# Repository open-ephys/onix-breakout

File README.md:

# ONIX Breakout Board
This board allows bench access to the IO provided by the [ONIX FMC Host
Board](https://github.com/open-ephys/onix-fmc-host). It features:

- 4x coax headstage ports, each with a physical power switch
- BNC, IDC (ribbon), or direct wire access to 12 analog inputs or outputs
- IDC (ribbon) or direct wire access to 8 digital outputs and 8 digital inputs
  (5 volt tolerate)
- 6x buttons for marking experimental events
- 41x state-indication LEDs
- 3x high-speed clock feed throughs
- Full-speed, USB 2.0 access to the onboard [TinyFPGA
  BX](https://www.crowdsupply.com/tinyfpga/tinyfpga-bx) for communication,
  programming, and customization 
- [HARP bus](https://www.cf-hw.org/harp)
- Rugged M6 or 1/4-20 mounting options compliant with 19" racks and optical
  tables
- Open-source [gateware](./gateware) created using open-source FPGA toolchain:
  [yosys](http://www.clifford.at/yosys/) & [nextpnr](https://github.com/YosysHQ/nextpnr)

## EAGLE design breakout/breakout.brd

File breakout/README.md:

## Bill of Materials
The bill of materials for this device can be found
[here](https://docs.google.com/spreadsheets/d/1dZ0ANEF8czLGsupTHfIfsVSbmfPmiTM9wAFmvc-KBbU/edit?usp=sharing).

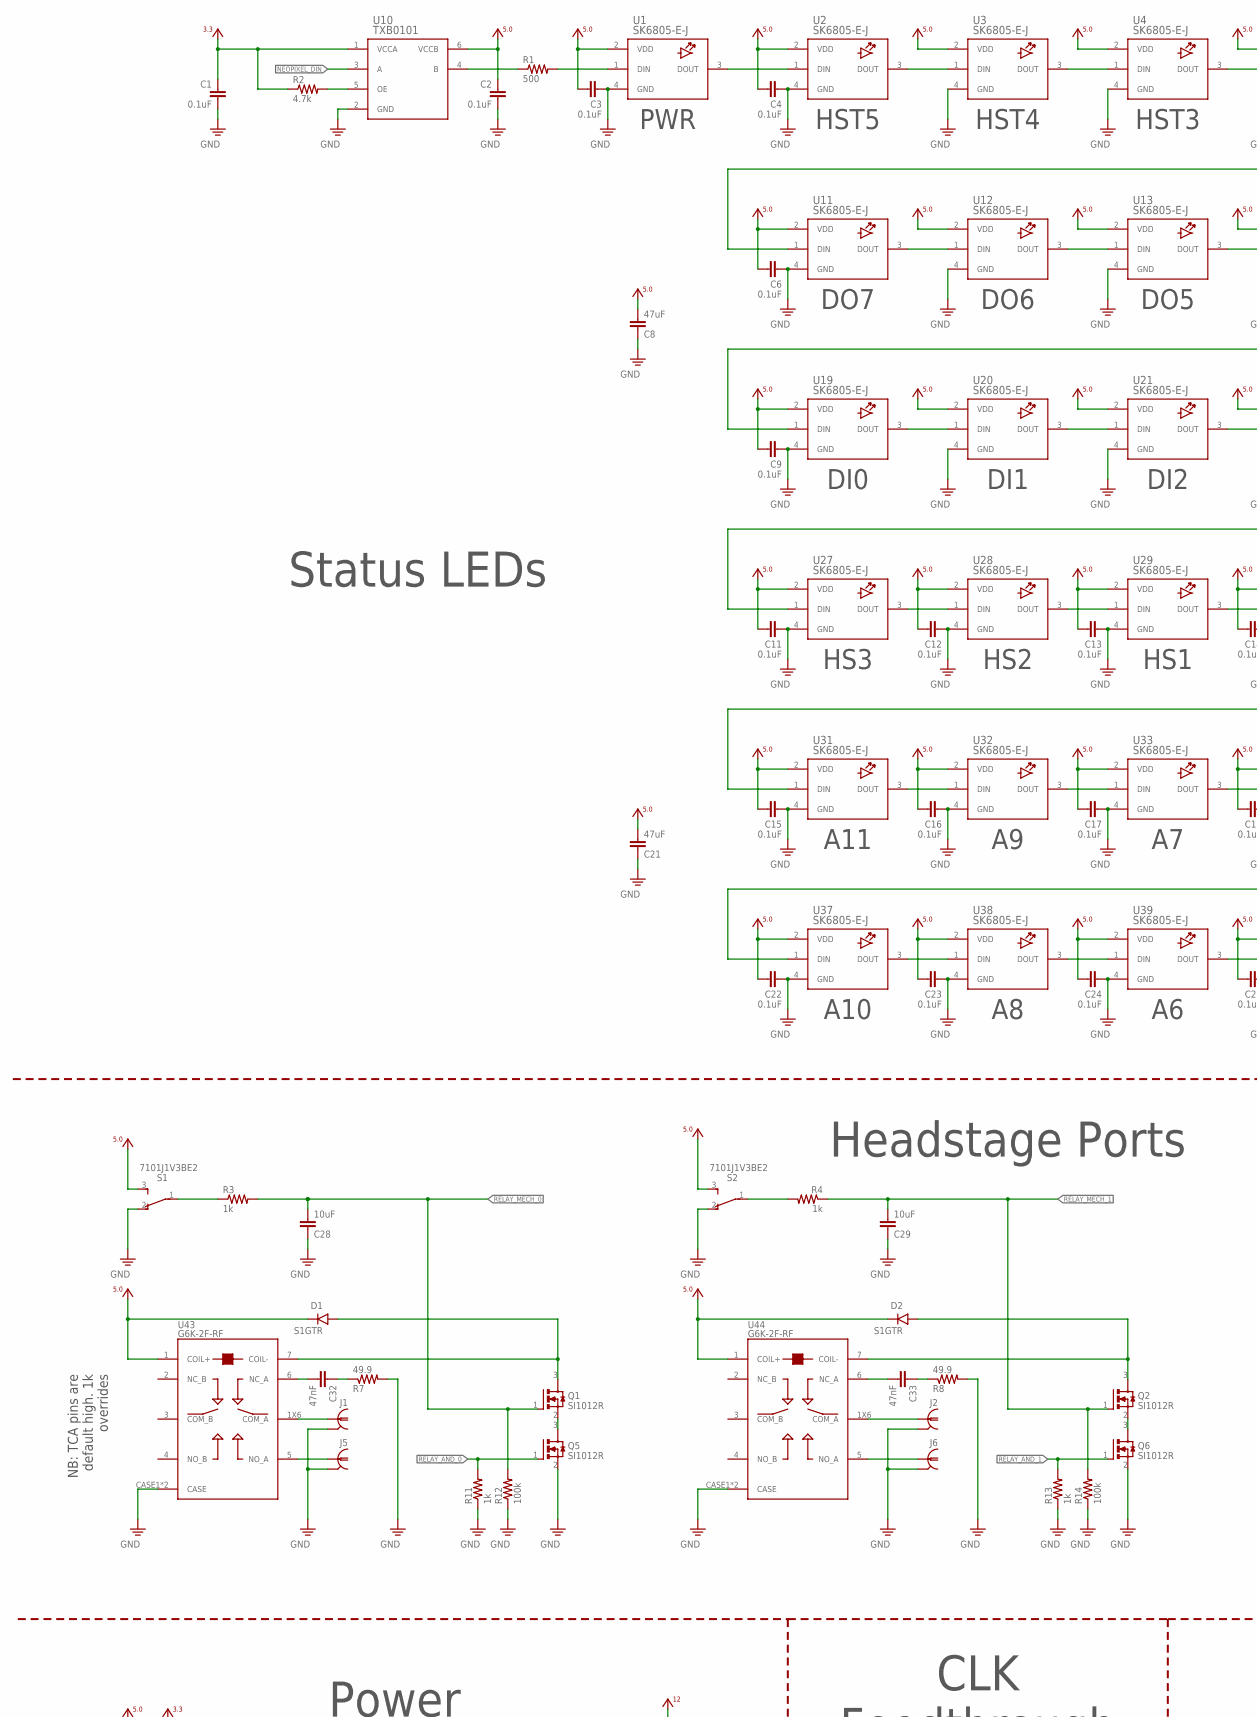
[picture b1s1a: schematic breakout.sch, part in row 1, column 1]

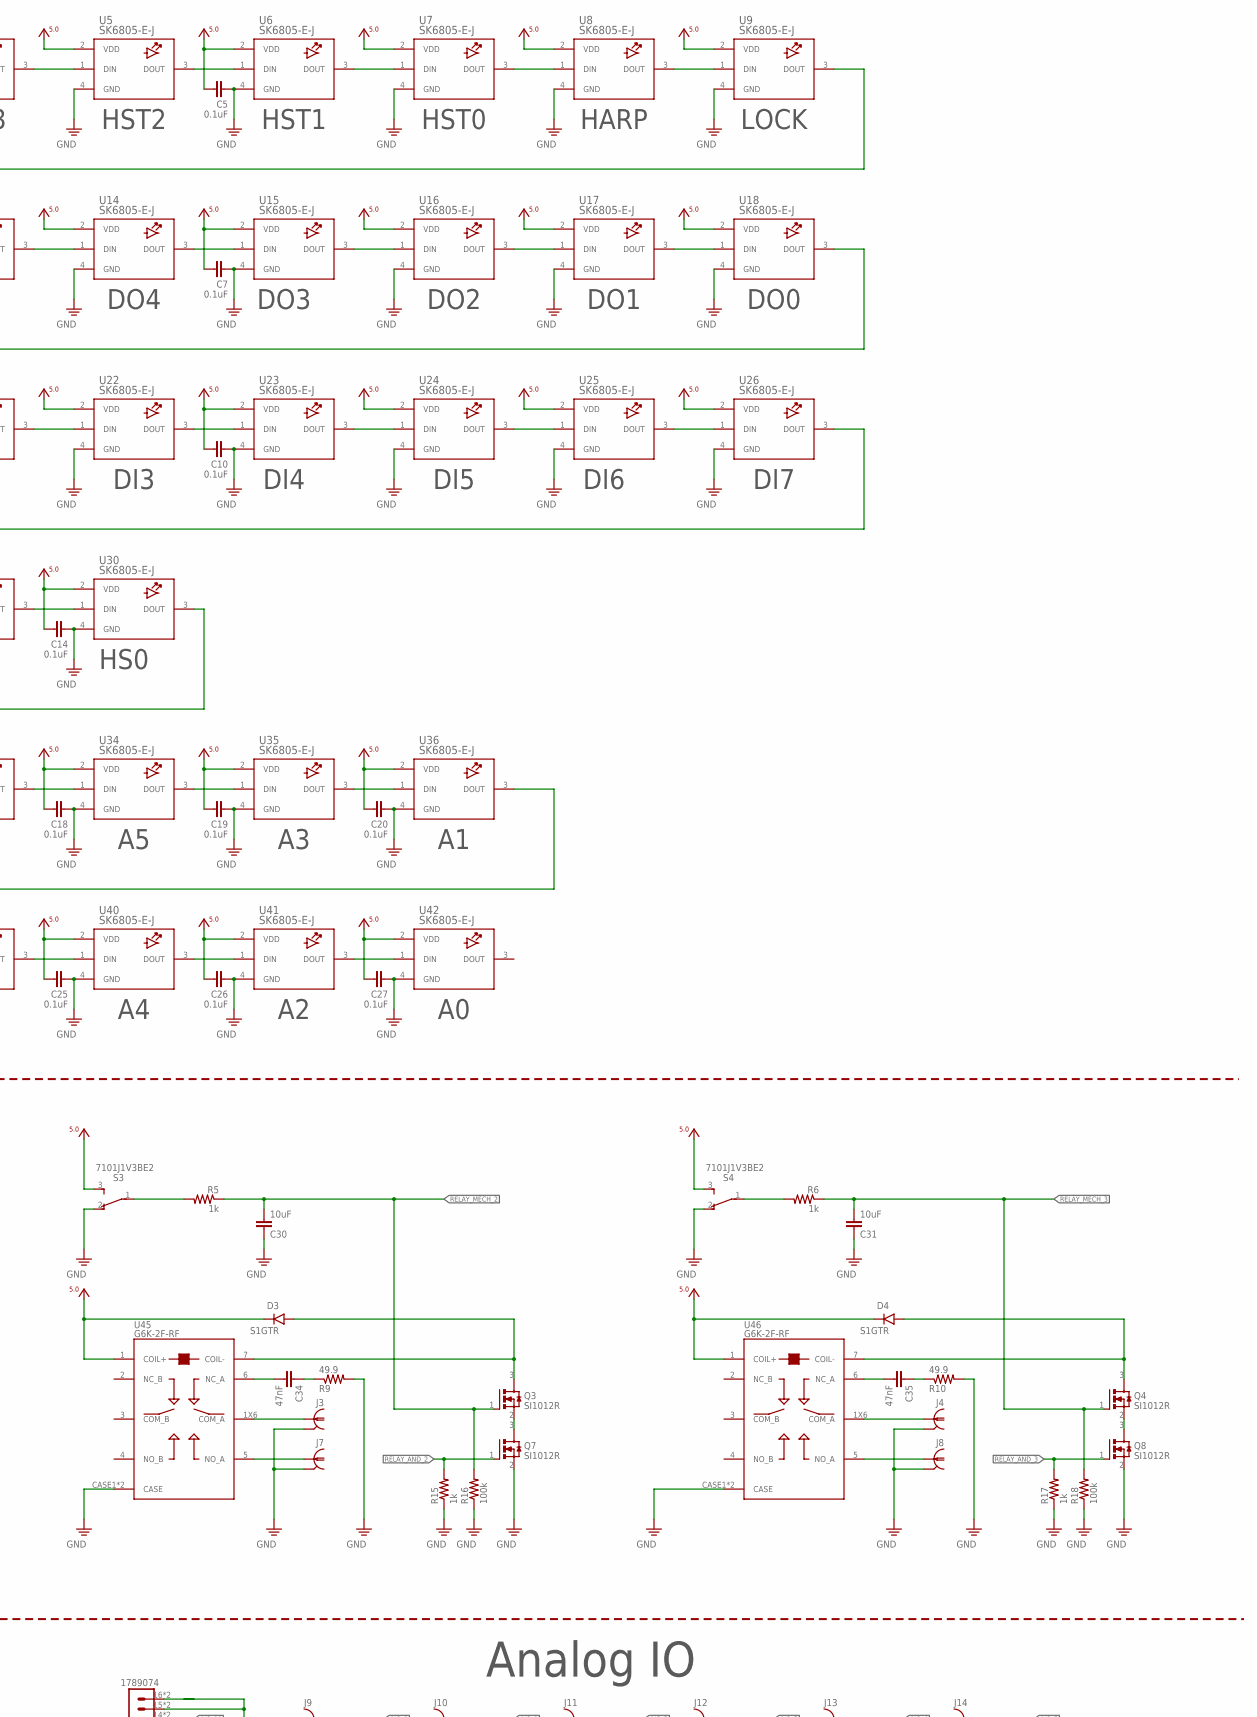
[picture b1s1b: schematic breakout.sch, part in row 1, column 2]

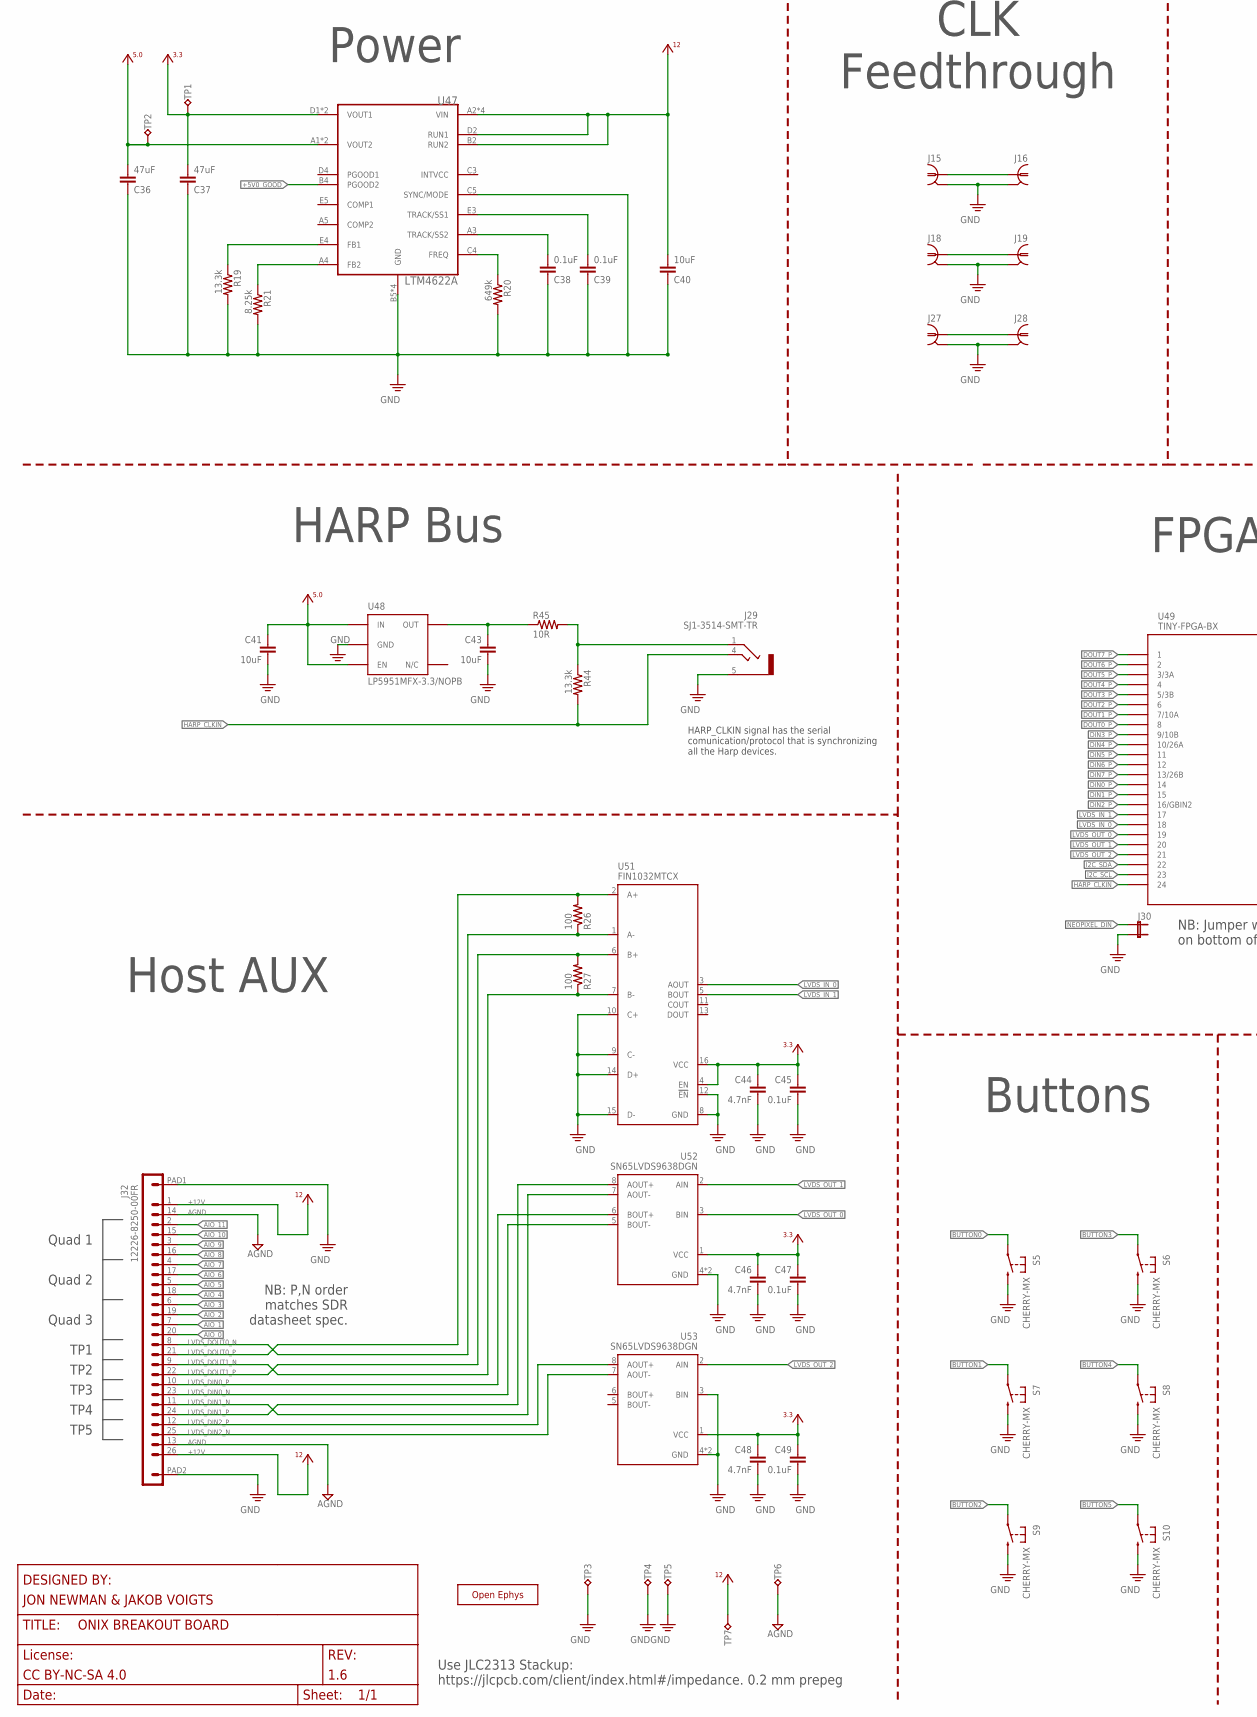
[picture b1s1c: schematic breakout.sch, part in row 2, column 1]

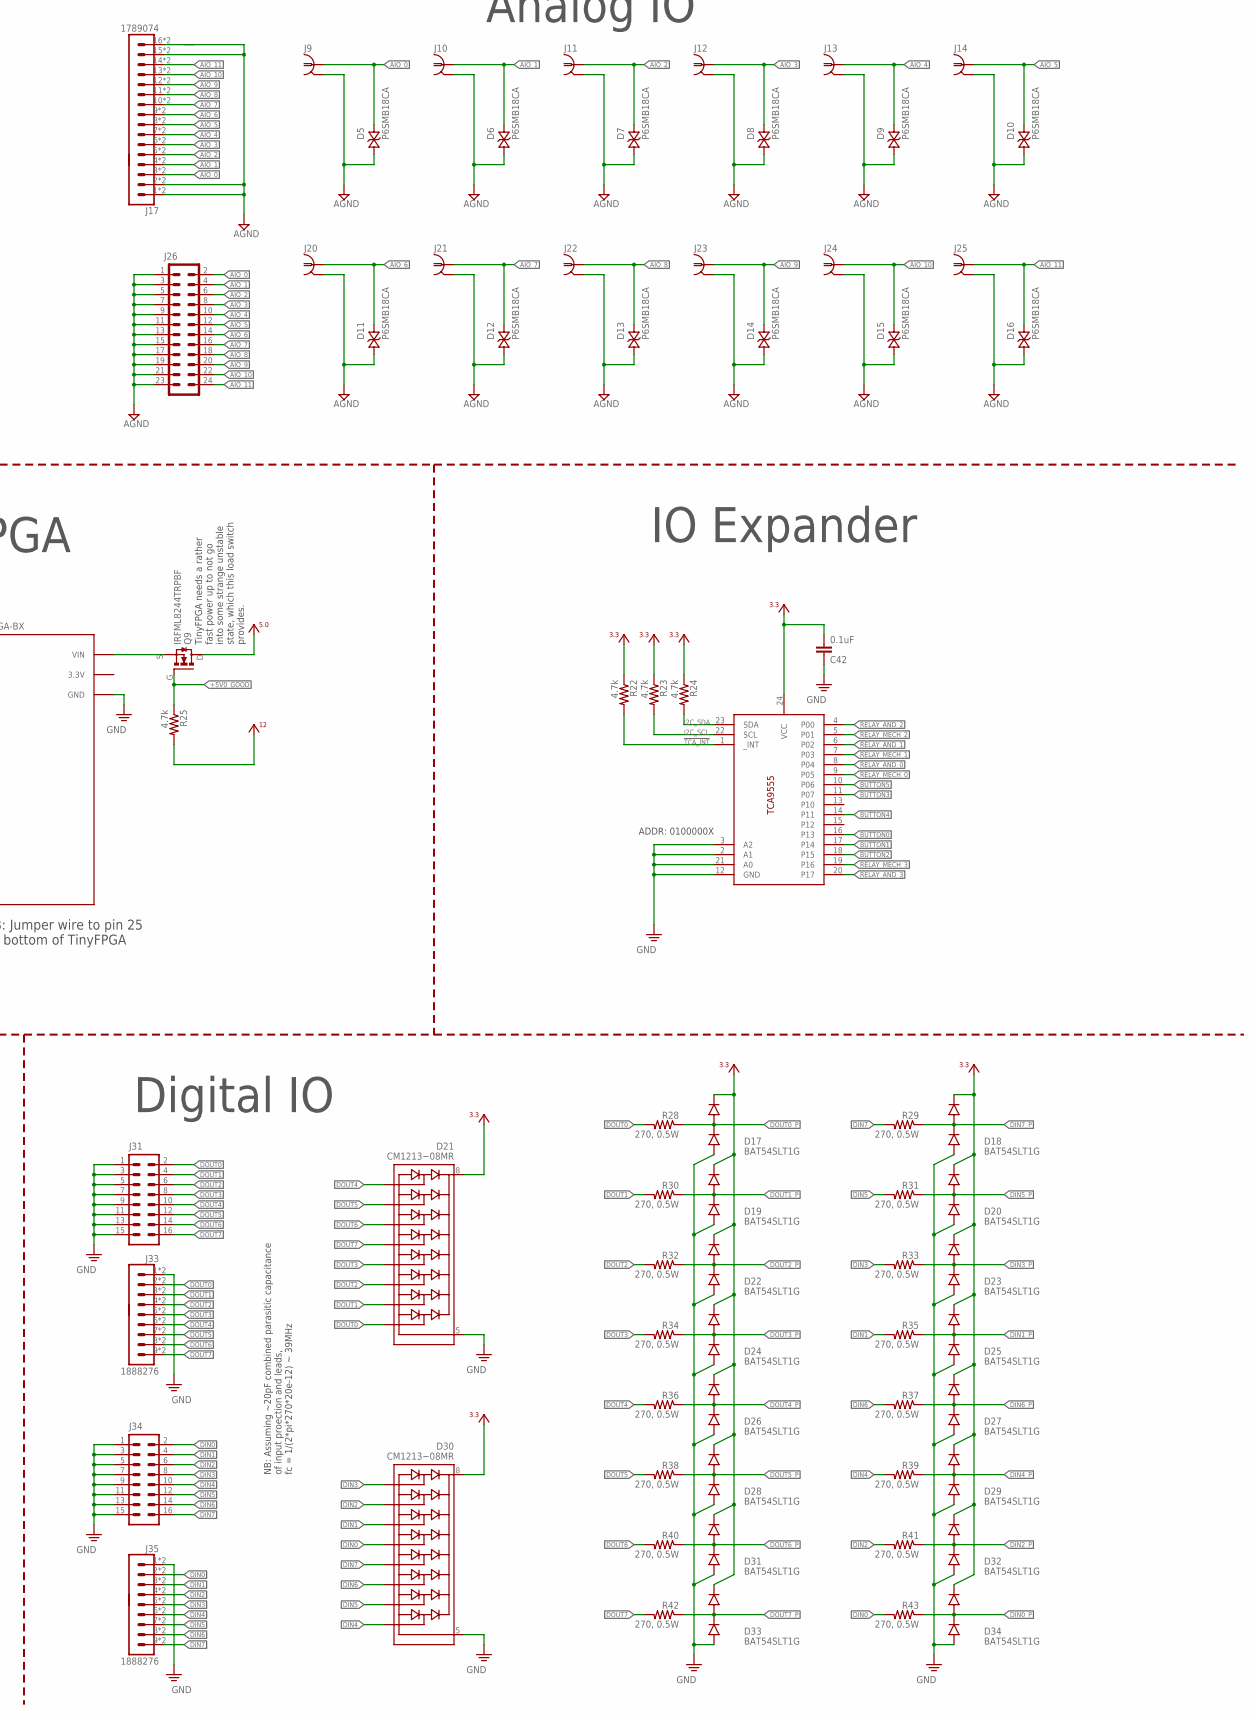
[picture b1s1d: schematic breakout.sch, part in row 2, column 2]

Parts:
C1, C2, C3, C4, C5, C6, C7, C9, C10, C11, C12, C13, C14, C15, C16, C17, C18, C19, C20, C22, C23, C24, C25, C26, C27, C38, C39, C42, C45, C47, C49: 0.1uF; 0402
C8, C21, C36, C37: 47uF; 1210
C28, C29, C30, C31, C40, C41, C43: 10uF; 0805
C32, C33, C34, C35: 47nF; 0402
C44, C46, C48: 4.7nF; 0402
D1, D2, D3, D4: S1GTR; SMA-DO214AC
D5, D6, D7, D8, D9, D10, D11, D12, D13, D14, D15, D16: P6SMB18CA; SMA-DO214AC
D17, D18, D19, D20, D22, D23, D24, D25, D26, D27, D28, D29, D31, D32, D33, D34: BAT54SLT1G; SOT23
D21, D30: CM1213−08MR; MSOP-10-3X3
J1, J2, J3, J4, J16, J19, J28: COAX_SMA-VERT; SMA_JACK_142-0701-201
J5, J6, J7, J8, J15, J18, J27: COAX_MMCX-THRU; MMCX-THRU
J9, J10, J11, J12, J13, J14, J20, J21, J22, J23, J24, J25: COAX_0731010360; 0731010360
J17: 1789074; SCREW16-2
J26: 69168-124HLF; 2X12-BIG
J29: SJ1-3514-SMT-TR; 35RASMT2BHNTRX
J30: JP2E_THRU-HOLE; JP2
J31, J34: 69168-116HLF; 2X08-BIG
J32: 12226-8250-00FR; 12226-82X0-00XX
J33, J35: 1888276; SCREW9-2
Q1, Q2, Q3, Q4, Q5, Q6, Q7, Q8: SI1012R; SC75
Q9: IRFML8244TRPBF; SOT23-GSD
R1: 500; 0402
R2, R22, R23, R24, R25: 4.7k; 0402
R3, R4, R5, R6, R11, R13, R15, R17: 1k; 0402
R7, R8, R9, R10: 49.9; 0402
R12, R14, R16, R18: 100k; 0402
R19, R44: 13.3k; 0402
R20: 649k; 0402
R21: 8.25k; 0402
R26, R27: 100; 0402
R28, R29, R30, R31, R32, R33, R34, R35, R36, R37, R38, R39, R40, R41, R42, R43: 270, 0.5W; 0805
R45: 10R; 0402
S1, S2, S3, S4: 7101J1V3BE2; CK_7101J1V3QE2
S5, S6, S7, S8, S9, S10: CHERRY-MX
TP1, TP2: TPTP19R; TP19R
TP3, TP4, TP5, TP6, TP7: TP_2MM; TESTPOINT_2MM
U1, U2, U3, U4, U5, U6, U7, U8, U9, U11, U12, U13, U14, U15, U16, U17, U18, U19, U20, U21, U22, U23, U24, U25, U26, U27, U28, U29, U30, U31, U32, U33, U34, U35, U36, U37, U38, U39, U40, U41, U42: SK6805-E-J; NEOPIXEL-1.5X1.5
U10: TXB0101; SOT23-6
U43, U44, U45, U46: G6K-2F-RF; G6KU-2F-RF
U47: LTM4622A; BGA_5X5_625X625
U48: LP5951MFX-3.3/NOPB; TSOT23-5; MPN TLV70033DDCR
U49: TINY-FPGA-BX; TINY-FPGA-BX_BASIC
U50: TCA9555; TSSOP-24
U51: FIN1032MTCX; TSSOP-16
U52, U53: SN65LVDS9638DGN; MSOP-8-PAD-3X3
X: OE-LOGO_28X20; OE-LOGO-28X20

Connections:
!TCA_INT: R22.2, U50.1 (_INT)
+3V3: C1.1, C37.2, C42.2, C44.1, C45.1, C46.1, C47.1, C48.1, C49.1, D17.2 (C), D18.2 (C), D19.2 (C), D20.2 (C), D21.8 (VCC), D22.2 (C), D23.2 (C), D24.2 (C), D25.2 (C), D26.2 (C), D27.2 (C), D28.2 (C), D29.2 (C), D30.8 (VCC), D31.2 (C), D32.2 (C), D33.2 (C), D34.2 (C), R2.1, R22.1, R23.1, R24.1, TP1.TP, U10.1 (VCCA), U47.D1 (VOUT1), U47.E1 (VOUT1), U50.24 (VCC), U51.4 (EN), U51.16 (VCC), U52.1 (VCC), U53.1 (VCC)
+5V0: C2.1, C3.2, C4.2, C5.2, C6.2, C7.2, C8.2, C9.2, C10.2, C11.2, C12.2, C13.2, C14.2, C15.2, C16.2, C17.2, C18.2, C19.2, C20.2, C21.2, C22.2, C23.2, C24.2, C25.2, C26.2, C27.2, C36.2, C41.1, D1.C, D2.C, D3.C, D4.C, Q9.D, S1.3, S2.3, S3.3, S4.3, TP2.TP, U1.2 (VDD), U2.2 (VDD), U3.2 (VDD), U4.2 (VDD), U5.2 (VDD), U6.2 (VDD), U7.2 (VDD), U8.2 (VDD), U9.2 (VDD), U10.6 (VCCB), U11.2 (VDD), U12.2 (VDD), U13.2 (VDD), U14.2 (VDD), U15.2 (VDD), U16.2 (VDD), U17.2 (VDD), U18.2 (VDD), U19.2 (VDD), U20.2 (VDD), U21.2 (VDD), U22.2 (VDD), U23.2 (VDD), U24.2 (VDD), U25.2 (VDD), U26.2 (VDD), U27.2 (VDD), U28.2 (VDD), U29.2 (VDD), U30.2 (VDD), U31.2 (VDD), U32.2 (VDD), U33.2 (VDD), U34.2 (VDD), U35.2 (VDD), U36.2 (VDD), U37.2 (VDD), U38.2 (VDD), U39.2 (VDD), U40.2 (VDD), U41.2 (VDD), U42.2 (VDD), U43.1 (COIL+), U44.1 (COIL+), U45.1 (COIL+), U46.1 (COIL+), U47.A1 (VOUT2), U47.B1 (VOUT2), U48.1 (IN), U48.3 (EN)
+5V0_GOOD: Q9.G, R25.1, U47.B4 (PGOOD2)
+12V: C40.2, J32.1, J32.26, R25.2, TP7.1, U47.A2 (VIN), U47.B2 (RUN2), U47.B3 (VIN), U47.D2 (RUN1), U47.D3 (VIN), U47.E2 (VIN)
AGND: D5.A (1), D6.A (1), D7.A (1), D8.A (1), D9.A (1), D10.A (1), D11.A (1), D12.A (1), D13.A (1), D14.A (1), D15.A (1), D16.A (1), J9.2, J9.3 (2), J9.4 (2), J9.5 (2), J10.2, J10.3 (2), J10.4 (2), J10.5 (2), J11.2, J11.3 (2), J11.4 (2), J11.5 (2), J12.2, J12.3 (2), J12.4 (2), J12.5 (2), J13.2, J13.3 (2), J13.4 (2), J13.5 (2), J14.2, J14.3 (2), J14.4 (2), J14.5 (2), J17.1, J17.2, J17.15, J17.16, J17.17 (1), J17.18 (2), J17.31 (15), J17.32 (16), J20.2, J20.3 (2), J20.4 (2), J20.5 (2), J21.2, J21.3 (2), J21.4 (2), J21.5 (2), J22.2, J22.3 (2), J22.4 (2), J22.5 (2), J23.2, J23.3 (2), J23.4 (2), J23.5 (2), J24.2, J24.3 (2), J24.4 (2), J24.5 (2), J25.2, J25.3 (2), J25.4 (2), J25.5 (2), J26.1, J26.3, J26.5, J26.7, J26.9, J26.11, J26.13, J26.15, J26.17, J26.19, J26.21, J26.23, J32.13, J32.14, TP6.1
AIO_0: D5.C (2), J9.1, J17.3, J17.19 (3), J26.2, J32.20
AIO_1: D6.C (2), J10.1, J17.4, J17.20 (4), J26.4, J32.7
AIO_2: D7.C (2), J11.1, J17.5, J17.21 (5), J26.6, J32.19
AIO_3: D8.C (2), J12.1, J17.6, J17.22 (6), J26.8, J32.6
AIO_4: D9.C (2), J13.1, J17.7, J17.23 (7), J26.10, J32.18
AIO_5: D10.C (2), J14.1, J17.8, J17.24 (8), J26.12, J32.5
AIO_6: D11.C (2), J17.9, J17.25 (9), J20.1, J26.14, J32.17
AIO_7: D12.C (2), J17.10, J17.26 (10), J21.1, J26.16, J32.4
AIO_8: D13.C (2), J17.11, J17.27 (11), J22.1, J26.18, J32.16
AIO_9: D14.C (2), J17.12, J17.28 (12), J23.1, J26.20, J32.3
AIO_10: D15.C (2), J17.13, J17.29 (13), J24.1, J26.22, J32.15
AIO_11: D16.C (2), J17.14, J17.30 (14), J25.1, J26.24, J32.2
BUTTON0: S5.SW1, U50.16 (P13)
BUTTON1: S7.SW1, U50.17 (P14)
BUTTON2: S9.SW1, U50.18 (P15)
BUTTON3: S6.SW1, U50.11 (P07)
BUTTON4: S8.SW1, U50.14 (P11)
BUTTON5: S10.SW1, U50.10 (P06)
DIN0: D30.4 (CH4), J34.2, J35.2, J35.11 (2), R43.2
DIN0_P: D34.3 (COMM), R43.1, U49.14
DIN1: D30.3 (CH3), J34.4, J35.3, J35.12 (3), R35.2
DIN1_P: D25.3 (COMM), R35.1, U49.15
DIN2: D30.2 (CH2), J34.6, J35.4, J35.13 (4), R41.2
DIN2_P: D32.3 (COMM), R41.1, U49.16 (16/GBIN2)
DIN3: D30.1 (CH1), J34.8, J35.5, J35.14 (5), R33.2
DIN3_P: D23.3 (COMM), R33.1, U49.9 (9/10B)
DIN4: D30.10 (CH8), J34.10, J35.6, J35.15 (6), R39.2
DIN4_P: D29.3 (COMM), R39.1, U49.10 (10/26A)
DIN5: D30.9 (CH7), J34.12, J35.7, J35.16 (7), R31.2
DIN5_P: D20.3 (COMM), R31.1, U49.11
DIN6: D30.7 (CH6), J34.14, J35.8, J35.17 (8), R37.2
DIN6_P: D27.3 (COMM), R37.1, U49.12
DIN7: D30.6 (CH5), J34.16, J35.9, J35.18 (9), R29.2
DIN7_P: D18.3 (COMM), R29.1, U49.13 (13/26B)
DOUT0: D21.10 (CH8), J31.2, J33.2, J33.11 (2), R28.2
DOUT0_P: D17.3 (COMM), R28.1, U49.8
DOUT1: D21.9 (CH7), J31.4, J33.3, J33.12 (3), R30.2
DOUT1_P: D19.3 (COMM), R30.1, U49.7 (7/10A)
DOUT2: D21.7 (CH6), J31.6, J33.4, J33.13 (4), R32.2
DOUT2_P: D22.3 (COMM), R32.1, U49.6
DOUT3: D21.6 (CH5), J31.8, J33.5, J33.14 (5), R34.2
DOUT3_P: D24.3 (COMM), R34.1, U49.5 (5/3B)
DOUT4: D21.1 (CH1), J31.10, J33.6, J33.15 (6), R36.2
DOUT4_P: D26.3 (COMM), R36.1, U49.4
DOUT5: D21.2 (CH2), J31.12, J33.7, J33.16 (7), R38.2
DOUT5_P: D28.3 (COMM), R38.1, U49.3 (3/3A)
DOUT6: D21.3 (CH3), J31.14, J33.8, J33.17 (8), R40.2
DOUT6_P: D31.3 (COMM), R40.1, U49.2
DOUT7: D21.4 (CH4), J31.16, J33.9, J33.18 (9), R42.2
DOUT7_P: D33.3 (COMM), R42.1, U49.1
GND: C1.2, C2.2, C3.1, C4.1, C5.1, C6.1, C7.1, C8.1, C9.1, C10.1, C11.1, C12.1, C13.1, C14.1, C15.1, C16.1, C17.1, C18.1, C19.1, C20.1, C21.1, C22.1, C23.1, C24.1, C25.1, C26.1, C27.1, C28.1, C29.1, C30.1, C31.1, C36.1, C37.1, C38.1, C39.1, C40.1, C41.2, C42.1, C43.2, C44.2, C45.2, C46.2, C47.2, C48.2, C49.2, D17.1 (A), D18.1 (A), D19.1 (A), D20.1 (A), D21.5 (VSS), D22.1 (A), D23.1 (A), D24.1 (A), D25.1 (A), D26.1 (A), D27.1 (A), D28.1 (A), D29.1 (A), D30.5 (VSS), D31.1 (A), D32.1 (A), D33.1 (A), D34.1 (A), J1.GND$1 (2), J1.GND$2 (2), J1.GND$3 (2), J1.GND$4 (2), J2.GND$1 (2), J2.GND$2 (2), J2.GND$3 (2), J2.GND$4 (2), J3.GND$1 (2), J3.GND$2 (2), J3.GND$3 (2), J3.GND$4 (2), J4.GND$1 (2), J4.GND$2 (2), J4.GND$3 (2), J4.GND$4 (2), J5.GND@1 (2), J5.GND@2 (2), J5.GND@3 (2), J5.GND@4 (2), J6.GND@1 (2), J6.GND@2 (2), J6.GND@3 (2), J6.GND@4 (2), J7.GND@1 (2), J7.GND@2 (2), J7.GND@3 (2), J7.GND@4 (2), J8.GND@1 (2), J8.GND@2 (2), J8.GND@3 (2), J8.GND@4 (2), J15.GND@1 (2), J15.GND@2 (2), J15.GND@3 (2), J15.GND@4 (2), J16.GND$1 (2), J16.GND$2 (2), J16.GND$3 (2), J16.GND$4 (2), J18.GND@1 (2), J18.GND@2 (2), J18.GND@3 (2), J18.GND@4 (2), J19.GND$1 (2), J19.GND$2 (2), J19.GND$3 (2), J19.GND$4 (2), J27.GND@1 (2), J27.GND@2 (2), J27.GND@3 (2), J27.GND@4 (2), J28.GND$1 (2), J28.GND$2 (2), J28.GND$3 (2), J28.GND$4 (2), J29.5, J30.2, J31.1, J31.3, J31.5, J31.7, J31.9, J31.11, J31.13, J31.15, J32.PAD1, J32.PAD2, J33.1, J33.10 (1), J34.1, J34.3, J34.5, J34.7, J34.9, J34.11, J34.13, J34.15, J35.1, J35.10 (1), Q5.2 (S), Q6.2 (S), Q7.2 (S), Q8.2 (S), R7.2, R8.2, R9.2, R10.2, R11.1, R12.1, R13.1, R14.1, R15.1, R16.1, R17.1, R18.1, R19.2, R20.2, R21.2, S1.2 (1), S2.2 (1), S3.2 (1), S4.2 (1), S5.SW2 (S), S6.SW2 (S), S7.SW2 (S), S8.SW2 (S), S9.SW2 (S), S10.SW2 (S), TP3.1, TP4.1, TP5.1, U1.4 (GND), U2.4 (GND), U3.4 (GND), U4.4 (GND), U5.4 (GND), U6.4 (GND), U7.4 (GND), U8.4 (GND), U9.4 (GND), U10.2 (GND), U11.4 (GND), U12.4 (GND), U13.4 (GND), U14.4 (GND), U15.4 (GND), U16.4 (GND), U17.4 (GND), U18.4 (GND), U19.4 (GND), U20.4 (GND), U21.4 (GND), U22.4 (GND), U23.4 (GND), U24.4 (GND), U25.4 (GND), U26.4 (GND), U27.4 (GND), U28.4 (GND), U29.4 (GND), U30.4 (GND), U31.4 (GND), U32.4 (GND), U33.4 (GND), U34.4 (GND), U35.4 (GND), U36.4 (GND), U37.4 (GND), U38.4 (GND), U39.4 (GND), U40.4 (GND), U41.4 (GND), U42.4 (GND), U43.CASE1 (CASE), U43.CASE2 (CASE), U44.CASE1 (CASE), U44.CASE2 (CASE), U45.CASE1 (CASE), U45.CASE2 (CASE), U46.CASE1 (CASE), U46.CASE2 (CASE), U47.B5 (GND), U47.C1 (GND), U47.C2 (GND), U47.C5 (SYNC/MODE), U47.D5 (GND), U48.2 (GND), U49.GND@1 (GND), U49.GND@2 (GND), U50.2 (A1), U50.3 (A2), U50.12 (GND), U50.21 (A0), U51.8 (GND), U51.9 (C-), U51.10 (C+), U51.12 (!EN), U51.14 (D+), U51.15 (D-), U52.4 (GND), U52.PAD (GND), U53.3 (BIN), U53.4 (GND), U53.PAD (GND)
HARP_CLKIN: J29.4, R44.2, U49.24
I2C_SCL: R23.2, U49.23, U50.22 (SCL)
I2C_SDA: R24.2, U49.22, U50.23 (SDA)
LOCKED: U9.3 (DOUT), U11.1 (DIN)
LVDS_DIN0_N: J32.23, U52.5 (BOUT-)
LVDS_DIN0_P: J32.10, U52.6 (BOUT+)
LVDS_DIN1_N: J32.11, U52.7 (AOUT-)
LVDS_DIN1_P: J32.24, U52.8 (AOUT+)
LVDS_DIN2_N: J32.25, U53.7 (AOUT-)
LVDS_DIN2_P: J32.12, U53.8 (AOUT+)
LVDS_DOUT0_N: J32.8, R26.1, U51.1 (A-)
LVDS_DOUT0_P: J32.21, R26.2, U51.2 (A+)
LVDS_DOUT1_N: J32.9, R27.1, U51.7 (B-)
LVDS_DOUT1_P: J32.22, R27.2, U51.6 (B+)
LVDS_IN_0: U49.18, U51.3 (AOUT)
LVDS_IN_1: U49.17, U51.5 (BOUT)
LVDS_OUT_0: U49.19, U52.3 (BIN)
LVDS_OUT_1: U49.20, U52.2 (AIN)
LVDS_OUT_2: U49.21, U53.2 (AIN)
unnamed: J15.SIG (1), J16.CLK (1)
unnamed: J18.SIG (1), J19.CLK (1)
unnamed: J27.SIG (1), J28.CLK (1)
unnamed: D1.A, Q1.3 (D), U43.7 (COIL-)
unnamed: Q1.2 (S), Q5.3 (D)
unnamed: U11.3 (DOUT), U12.1 (DIN)
unnamed: U12.3 (DOUT), U13.1 (DIN)
unnamed: U13.3 (DOUT), U14.1 (DIN)
unnamed: U36.3 (DOUT), U37.1 (DIN)
unnamed: U31.3 (DOUT), U32.1 (DIN)
unnamed: D2.A, Q2.3 (D), U44.7 (COIL-)
unnamed: U15.3 (DOUT), U16.1 (DIN)
unnamed: U16.3 (DOUT), U17.1 (DIN)
unnamed: C32.2, U43.6 (NC_A)
unnamed: J29.1, R44.1, R45.2
unnamed: J6.SIG (1), U44.5 (NO_A)
unnamed: U17.3 (DOUT), U18.1 (DIN)
unnamed: U1.3 (DOUT), U2.1 (DIN)
unnamed: C33.1, R8.1
unnamed: R3.1, S1.1 (2)
unnamed: R21.1, U47.A4 (FB2)
unnamed: R19.1, U47.E4 (FB1)
unnamed: C38.2, U47.A3 (TRACK/SS2)
unnamed: C39.2, U47.E3 (TRACK/SS1)
unnamed: J5.SIG (1), U43.5 (NO_A)
unnamed: J1.CLK (1), U43.1X6 (COM_A)
unnamed: C32.1, R7.1
unnamed: C33.2, U44.6 (NC_A)
unnamed: Q3.2 (S), Q7.3 (D)
unnamed: C34.1, R9.1
unnamed: J2.CLK (1), U44.1X6 (COM_A)
unnamed: R4.2, S2.1 (2)
unnamed: C34.2, U45.6 (NC_A)
unnamed: J7.SIG (1), U45.5 (NO_A)
unnamed: R5.2, S3.1 (2)
unnamed: Q2.2 (S), Q6.3 (D)
unnamed: U2.3 (DOUT), U3.1 (DIN)
unnamed: U3.3 (DOUT), U4.1 (DIN)
unnamed: J3.CLK (1), U45.1X6 (COM_A)
unnamed: R6.2, S4.1 (2)
unnamed: C35.1, R10.1
unnamed: C35.2, U46.6 (NC_A)
unnamed: J8.SIG (1), U46.5 (NO_A)
unnamed: J4.CLK (1), U46.1X6 (COM_A)
unnamed: U4.3 (DOUT), U5.1 (DIN)
unnamed: D3.A, Q3.3 (D), U45.7 (COIL-)
unnamed: U6.3 (DOUT), U7.1 (DIN)
unnamed: U7.3 (DOUT), U8.1 (DIN)
unnamed: U8.3 (DOUT), U9.1 (DIN)
unnamed: R1.2, U1.1 (DIN)
unnamed: R1.1, U10.4 (B)
unnamed: U5.3 (DOUT), U6.1 (DIN)
unnamed: R2.2, U10.5 (OE)
unnamed: U14.3 (DOUT), U15.1 (DIN)
unnamed: D4.A, Q4.3 (D), U46.7 (COIL-)
unnamed: Q4.2 (S), Q8.3 (D)
unnamed: Q9.S, U49.VIN
unnamed: U32.3 (DOUT), U33.1 (DIN)
unnamed: U33.3 (DOUT), U34.1 (DIN)
unnamed: U34.3 (DOUT), U35.1 (DIN)
unnamed: U35.3 (DOUT), U36.1 (DIN)
unnamed: U37.3 (DOUT), U38.1 (DIN)
unnamed: U38.3 (DOUT), U39.1 (DIN)
unnamed: U39.3 (DOUT), U40.1 (DIN)
unnamed: U40.3 (DOUT), U41.1 (DIN)
unnamed: U41.3 (DOUT), U42.1 (DIN)
unnamed: U18.3 (DOUT), U19.1 (DIN)
unnamed: U19.3 (DOUT), U20.1 (DIN)
unnamed: U20.3 (DOUT), U21.1 (DIN)
unnamed: U21.3 (DOUT), U22.1 (DIN)
unnamed: U22.3 (DOUT), U23.1 (DIN)
unnamed: U23.3 (DOUT), U24.1 (DIN)
unnamed: U24.3 (DOUT), U25.1 (DIN)
unnamed: U25.3 (DOUT), U26.1 (DIN)
unnamed: U26.3 (DOUT), U27.1 (DIN)
unnamed: U27.3 (DOUT), U28.1 (DIN)
unnamed: U28.3 (DOUT), U29.1 (DIN)
unnamed: U29.3 (DOUT), U30.1 (DIN)
unnamed: U30.3 (DOUT), U31.1 (DIN)
unnamed: C43.1, R45.1, U48.5 (OUT)
unnamed: R20.1, U47.C4 (FREQ)
NEOPIXEL_DIN: J30.1, U10.3 (A)
RELAY_AND_0: Q5.1 (G), R11.2, U50.8 (P04)
RELAY_AND_1: Q6.1 (G), R13.2, U50.6 (P02)
RELAY_AND_2: Q7.1 (G), R15.2, U50.4 (P00)
RELAY_AND_3: Q8.1 (G), R17.2, U50.20 (P17)
RELAY_MECH_0: C28.2, Q1.1 (G), R3.2, R12.2, U50.9 (P05)
RELAY_MECH_1: C29.2, Q2.1 (G), R4.1, R14.2, U50.7 (P03)
RELAY_MECH_2: C30.2, Q3.1 (G), R5.1, R16.2, U50.5 (P01)
RELAY_MECH_3: C31.2, Q4.1 (G), R6.1, R18.2, U50.19 (P16)

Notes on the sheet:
Use JLC2313 Stackup: https://jlcpcb.com/client/index.html#/impedance. 0.2 mm prepeg
NB: P,N order matches SDR datasheet spec.
Power
Host AUX
Headstage Ports
Analog IO
HARP_CLKIN signal has the serial comunication/protocol that is synchronizing all the Harp devices.
HARP Bus
CLK Feedthrough
Quad 1
Quad 2
Quad 3
TP1
TP2
TP3
TP4
TP5
IO Expander
Buttons
FPGA
Digital IO
Status LEDs
ADDR: 0100000X
NB: Assuming ~20pF combined parasitic capacitance of input proection and leads, fc = 1/(2*pi*270*20e-12) ~ 39MHz
NB: Jumper wire to pin 25 on bottom of TinyFPGA
PWR
HST0
HARP
LOCK
DO7
DO6
DO5
DO4
DO3
DO2
DO1
DO0
DI0
DI1
DI2

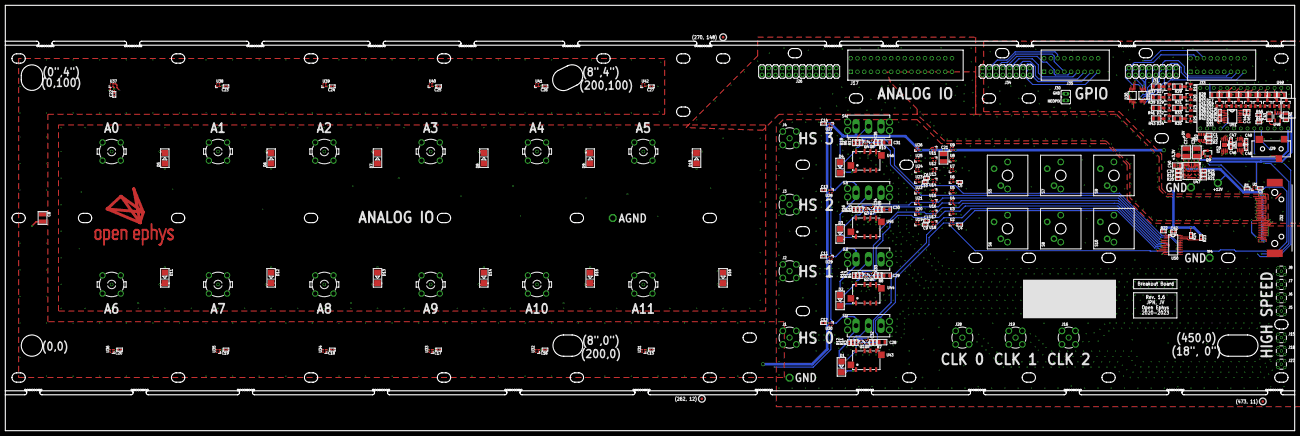
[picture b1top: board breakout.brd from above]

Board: 4 copper layers, 485.0 x 160.0 mm, 246 parts (0 on the bottom side), 166 nets.

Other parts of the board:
E$1, E$3, E$5: FIDUCIAL

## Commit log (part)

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2019-08-15 WIP on pcie system breakout board
    just started putting down some parts in the .sch and did some rough spacing tests
2019-08-16 Breakout board WIP
    - added shiftreg to read keys and relay status
    - added power supply
    - added relays
    - added lvds/se converters
2019-08-17 breakout board layout
    no routing but most of the basic connections are there
2019-08-17 Added teensy4 pinout to breakout board
2019-08-19 Breakout board WIP
    -Basic PCB should be there, some open questions (see note on sch)
    - very rough sketch of housing spacing
2019-08-21 Breakout WIP
    -Switched to PCB mounted switches
    -Moved cherry keypad further away
    -Added LP filters and flyback diodes to RF switches
2019-08-22 WIP breakout board
    -added Harp interface
    -added little sudio amp for mono speaker output
    -lots of other little stuff
    -2do: add speaker as well, for bleep bloops
2019-08-22 Added encoder to breakout board
2019-08-22 speaker for breakout board
    added .1" header for small 28ish mm diameter speakers ( 433-1220-ND etc)
2019-08-22 Adedd cutout for bigger skeaper to breakout board
    Should now barely fit a 2055-BGC-D40-22-4-002-ND
2019-08-24 Update breakout datasheet file names
    - Add human readable text to file names
2019-08-26 Breakout board layout and circuit fixes
    - Many fixes to schematic ERC and board layout
    - Added serial to parallel digital IO
2019-08-27 Final updates to breakout board r1.1 before fab
    - Fix OLED package
    - Double check teensy pins and update schematic with teensy 4.0 part
    - Minor routing changes
2019-08-30 Added some breakout case componnet models
2019-09-01 breakout case WIP
2019-09-01 More breakout board WIP
2019-09-03 Breakout board edits
    improved manufacturability by increasing interior corner radii etc
2019-09-05 More tweaks to breakout case
    Added more space for bottom side smd components
2019-09-05 Breakout board headphone/harp cutouts
2019-09-23 Breakout board revision 1.1
    - Small changes to layout, routing, and footprints after assembly of rev
    1.0
2019-09-29 Added CNCd PCIe bracket for FMC host
2019-10-07 Added some very rudimentary firmware for the breakout board
    - Display a main menu on the OLED using littlevgl
    - Control it with a rotary encoder
    - littlevgl config file is included and needs to be copied to the base
    directory of the littlevgl library before using this
2019-11-24 Breakout board revision 1.2
    - The breakout board is moving back to a much more passive device than
    in revision 1.0 and 1.1. The decision was made early for most logic to
    be carried out on host FMC board. We need to stick by this decision to
    prevent feature creep, maintenance issues, and synchronization bugs
    - Removed the OLED display
    - Removed rotary encoder
2019-12-28 WIP breakout board
    updated PCB dimensions and started re-arranging parts
    - 2do: add audio jack
    - 2do: update shell
    - 2do: update mounting holes
    - 2do: split into two parts
2020-01-10 Breakout board rev. 1.2 ready for production
    - Minor changes to ERC and schematic
2020-02-07 Updated PCIe mounting bracket
    - Increased FMC standoff form 10 to 12mm
    - Added holes for LEDs
    - Fixed markings
2020-04-02 Added RGB LEDs and driver to breakout-board
    - The old circuit, with single green LEDs driven by the TCA9555 is still
    there and functional if this circuit is not populated
    - If it is, the LED outputs on the TCA should be set to hiZ
2020-04-02 First commit of breakout board firmware
    - This is gateware for the TinyFPGA Bx on the breakout board
    - So far controls the TCA955 and provides serialzed digital data to
    host.
    - TODO is host to breakout communication (which will work very
    similarly), RGB LED driver, and HARP communication.
2020-04-25 Replaced RGB LED driver with neopixels
    - This way we can have all kinds of status indicators on the board
    - I added 41 of the 1.5x1.5mm neopixels for indicating power, harp, pll
    lock, digital in, digital out, and analog IO state
    - The control signal for these is going to have to come from one of the
    SMD pads on the bottom of the TinyFPGA Bx. I just put a general purpose
    jumper pad in there so that soder wire or 0.1" connector to wire can be
2020-04-25 Added uptated schematic for breakout board
2020-05-01 Added lightpipe cutouts to breakout case top
    - Added cutouts for lightpipes, for using 350-3723-ND
    in 6.35 (.25) and 15.24 (.6) mm heights see http://www.dialightsignalsandcomponents.com/Assets/Brochures_And_Catalogs/Indication/Opto_new/Dialight_CBI_data_515_OptoVPM_3mm_Jan2019.pdf
    - 2do: split bottom half
2020-05-27 Fixed typos in breakout board doc
2020-06-10 Added frozen breakout/revisions/rev-1.3
    - This was just sent out for production and therefore needs a revision
    here
    - Eventually, the firmware and case should be included in this revision
    folder once it has stabized
2020-06-10 Adde breakout html bom top level breakout folder
2020-07-02 clroni version 3.1.1
    - Replaced device map naming with device table
    - contex.DeviceTable is now a Dictionary rather than a List
    - Update nuget package
2020-07-26 Initial commit top label draft
    2do: almost everything
    this assumes a hard recessed sticker
2020-08-10 Change breakout board license to CC BY-NC-SA
2020-08-10 Initial commit of breakout rev 1.4
    - Fixes to analog routing to maintain consistancy of analog and digital
    pin ordering in the screw terminals and IDC headers
    - Switch the ordering of BNC analog connector to row major and aligned
    in column direction.
    - Add a secondary, internally controlled FET in series with the coil on
    each headstage relay so that certain ports can be disabled when
2020-08-28 Move entire repository to CC BY-NC-SA 4.0
2020-09-01 Minore updates to breakout rev 1.4
    - Address issues found during the construction of the case
    - DOUT IDC and terminal block switch positions to match the other two IO
    banks
2020-09-01 Breakout case WIP
    non functional, needs to be updated to newer pcb
2020-09-01 More updates to breakout rev. 1.4 to fit case
    - Swiched 2x 8 pin screw terminals for a single 16 pin screw terminal.
    - Moved m3 clearance holes in front of IDC connectors up a bit
2020-09-03 WIP breakout case
2020-09-04 Added waterejet DXF files for case to get quotes ready
2020-09-06 Breakout case 3d printed M3&M4 threads and split STLs
2020-09-24 Breakout board firmware update
    - Added host_to_breakout module for receiving GPIO and status
    information from host.
    - Added neopixel functionality and required libraries
    - Added Harp functionality
2020-10-07 Breakout board rev. 1.5
    - Very minor changes to 1.4 after a full fit test.
    - The M6/14-20 mount slots were made larger
    - The M3 holes were turned into slots to allow some slop
    - The power neopixel was moved down by 3.5 mm
2020-10-09 Increased space between IDC headers and wire terminals on breakout
    - Moved by 2mm so that an IDC connector can actually plug into the
    header.
2020-10-09 Updated case to fix a number of mechanics issues
2020-10-13 Breakout board revision 1.5
    - Ready for production
    - Added smd-mount folder with component positions
    - As soon as I get confirmation from Filipe I will freeze this in the
    revisions folder
2021-02-11 Added more room for caps in breakout case
    Changed circular cutouts on bottom side of the case facing the PCB to longer slots to make more room for components. Should fix issue that filipe just encountered on first test assembly for beta-test.
2021-03-15 Nearly feature complete breakout firmware
    - Passes timing at 60 MHz
    - Much improved neopixel control logic
    - Colors and dimming generated using colors.py and loaded into block RAM
    - Lots of other changes to get bidirectional communication working and
    robust.
    - Probably will need to play with color pallet to get it looking good.
2021-03-16 Added color block RAM initialization file
    - Added colors.mem so it does not need to be generated with colors.py to
    generate a bit file
    - Increase power-on & PLL-lock reset duration which seems to allow hot
    plugging of the SDR cable without issue
    - Other minor fixes
2021-03-16 Update breakout firmware README.md
    - Get rid of PLL info since its clearly visible in the code
2021-03-16 Added more tolerance to the case design
2021-03-17 Updated breakout case label
2021-03-22 Add post_assembly_test top level to breakout firmware
    - This top level enables all ports to allow testing of SERDES
    connectivity
    - It also sets both D_OUT and D_IN to outputs and puts them high so they
    can be probed to test connectivity
    - Neopixels are on and set to max brightness
    - Buttons have their normal function
2021-04-06 Fully functional breakout firmware
    - Integrated preprocessor switches into the code so that changes do not
    need to be made to run simulations
    - Digital input sampling now occurs on falling edge of LVDS_OUT[0] which
    put it 180 deg. out of phase with when its latched to prevent
    metastability
    - Other very small changes
2021-04-26 Remove incorrect link to BOM in breakout/README
    - Replace with a generic link to its documentation page.
    - This sould be done for all other boards at some point
2021-05-25 Rename breakout/firmware to breakout/gateware
2021-05-26 breakout rev. 1.6
    - Minor revision that addes a load switch driven by the LM4622's PGOOD2
    output between 5V and FPGA Vin. This improves the power-on behavior of
    the board and prevents it from entering an unstable state that requires
    a manual reset via pushing the reset button.
2021-05-26 Add IRFML8244 N-MOSFET datasheet to breakout/datasheets
2021-05-26 Update revision label on bottom of breakout board
    - There was a mismatch between current revision (1.6) and previous (1.5)
2021-07-13 Moved fmc-breakout into independent repo
    - Did some reorganization as well to make it a bit more like the
    onix-headstage-neuropix1 repo
2021-07-15 Minor updates during BOM creation.
    - Update PDF schematic
    - Update html BOM to rev 1.6
    - Update smd mount file.
    - Add breakout dir README
2021-07-19 Add .gitignore
    - Update schematic part numbers to match BOM
2021-07-27 Remove sad looking SDR connector from breakout image
2021-09-01 Add license
    - CC BY-NC-SA 4.0
2021-10-26 Add digital input synchronizer stages to improve performance and stability
2021-11-02 Replace LVDS protocol by a 60Mhz 8b10b scheme
2021-11-02 Fix switched digital inputs and output LED indicators
2021-11-02 Coding style changes during review
2022-06-26 Host and harp indication LEDs were swapped.
2022-06-29 Remove headstage ports C and D from case
    - We will not be populating them and they dont match the FMC board's IO
    - Clean up old files
2022-12-29 Updated the schematic to use Harp timestamp bus as input.
    The layout (.brd) is not ready yet.
    Replaced U48 SI8610 with U48 TLV70033DDCR (adds extra BOM line. PN TLV70033DDCR)
    Replaced C41 0402 0.1uF with C41 0805 10uF (same PN as C40 to not add extra BOM line)
    Replaced C43 0402 0.1uF with C43 0805 10uF (same PN as C40 to not add extra BOM line)
    Added R44 0402 13.3k (same PN as R19 to not add extra BOM line)
    Added R45 0402 10R (adds extra BOM line. PN CRCW040210R0FKEDHP)
2023-01-22 Updated the copyright year to "2020-2023".
2023-01-22 Updated to current schematic.
2023-01-22 Updated gerber files to current layout.
2023-01-23 Updated centroids to current layout.
2023-02-16 Changed separation method to mouse bites.
    The design of the functional circuitry of the PCB has no difference
    The previous commit can be used for production, it's the same board's revision.
2023-05-15 Increase diameter of SMA holes
    - For headstage and clock connections to prevent SMA shell from rubbing
    on case
2023-05-15 Add port warning sticker
2023-09-20 Update top_label_print.ai
    Updated .ai file for top label for print, not-editable, all fonts etc. fully vectorized
2023-09-21 removed MMCX C/D labels
2023-11-23 Modufy HARP port from output to input
2024-01-19 Fix LEDs not blinking without HARP producer
